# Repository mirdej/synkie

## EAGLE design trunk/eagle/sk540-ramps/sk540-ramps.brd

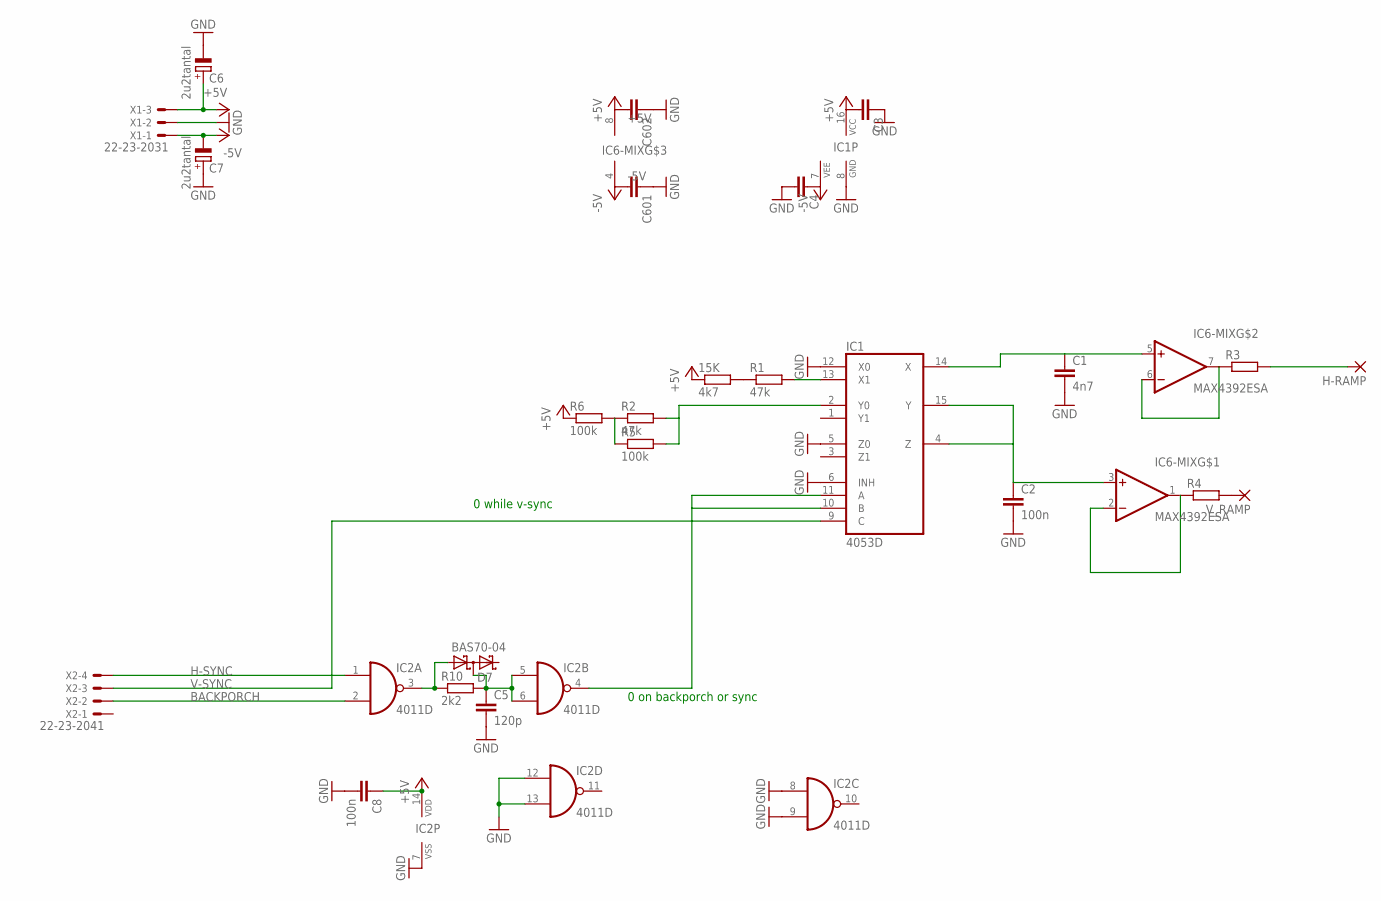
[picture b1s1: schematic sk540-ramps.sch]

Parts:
15K: 4k7; R1206
C1: 4n7; C1206
C2, C8: 100n; C1206
C3, C4, C601, C602: C-EUC1206; C1206
C5: 120p; C1206
C6, C7: 2u2tantal; CT3528
D7: BAS70-04; SOT23
H-RAMP: 3,17/1,1
IC1: 4053D; SO16
IC2: 4011D; SO14
IC6-MIX: MAX4392ESA; SO08
R1, R2: 47k; R1206
R3, R4: R-EU_R1206; R1206
R5, R6: 100k; R1206
R10: 2k2; R1206
V_RAMP: 3,17/1,1
X1: 22-23-2031
X2: 22-23-2041

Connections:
+5V: 15K.1, C3.2, C6.+, C8.1, C602.2, IC1.16 (VCC), IC2.14 (VDD), IC6-MIX.8 (+5V), R6.1, X1.3
-5V: C4.1, C7.-, C601.2, IC1.7 (VEE), IC6-MIX.4 (-5V), X1.1
BACKPORCH: IC2.2 (I1), X2.2
GND: C1.2, C2.2, C3.1, C4.2, C5.2, C6.-, C7.+, C8.2, C601.1, C602.1, IC1.5 (Z0), IC1.6 (INH), IC1.8 (GND), IC1.12 (X0), IC2.7 (VSS), IC2.8 (I0), IC2.9 (I1), IC2.12 (I0), IC2.13 (I1), X1.2
H-SYNC: IC2.1 (I0), X2.4
unnamed: 15K.2, R1.1
unnamed: R2.1, R5.1, R6.2
unnamed: C5.1, D7.3 (C1A2), IC2.5 (I0), IC2.6 (I1), R10.2
unnamed: IC1.10 (B), IC1.11 (A), IC2.4 (O)
unnamed: C1.1, IC1.14 (X), IC6-MIX.5 (+IN)
unnamed: IC6-MIX.6 (-IN), IC6-MIX.7 (OUT), R3.1
unnamed: H-RAMP.1, R3.2
unnamed: C2.1, IC1.4 (Z), IC1.15 (Y), IC6-MIX.3 (+IN)
unnamed: IC6-MIX.1 (OUT), IC6-MIX.2 (-IN), R4.1
unnamed: R4.2, V_RAMP.1
unnamed: D7.1 (A1), IC2.3 (O), R10.1
unnamed: IC1.13 (X1), R1.2
unnamed: IC1.2 (Y0), R2.2, R5.2
V-SYNC: IC1.9 (C), X2.3

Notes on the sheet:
0 on backporch or sync
0 while v-sync

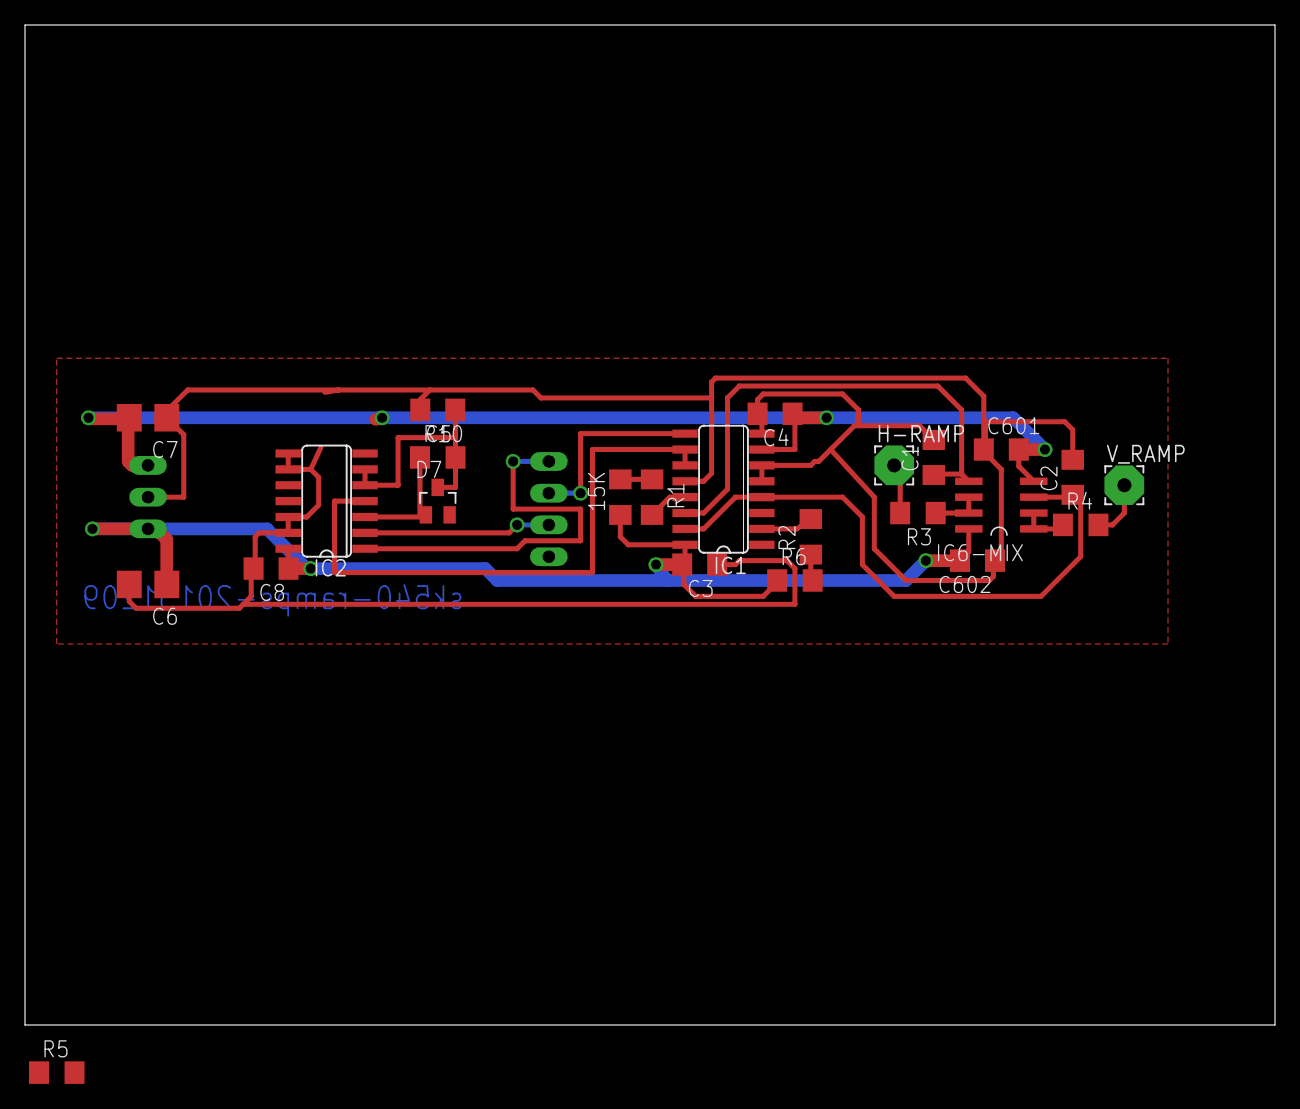
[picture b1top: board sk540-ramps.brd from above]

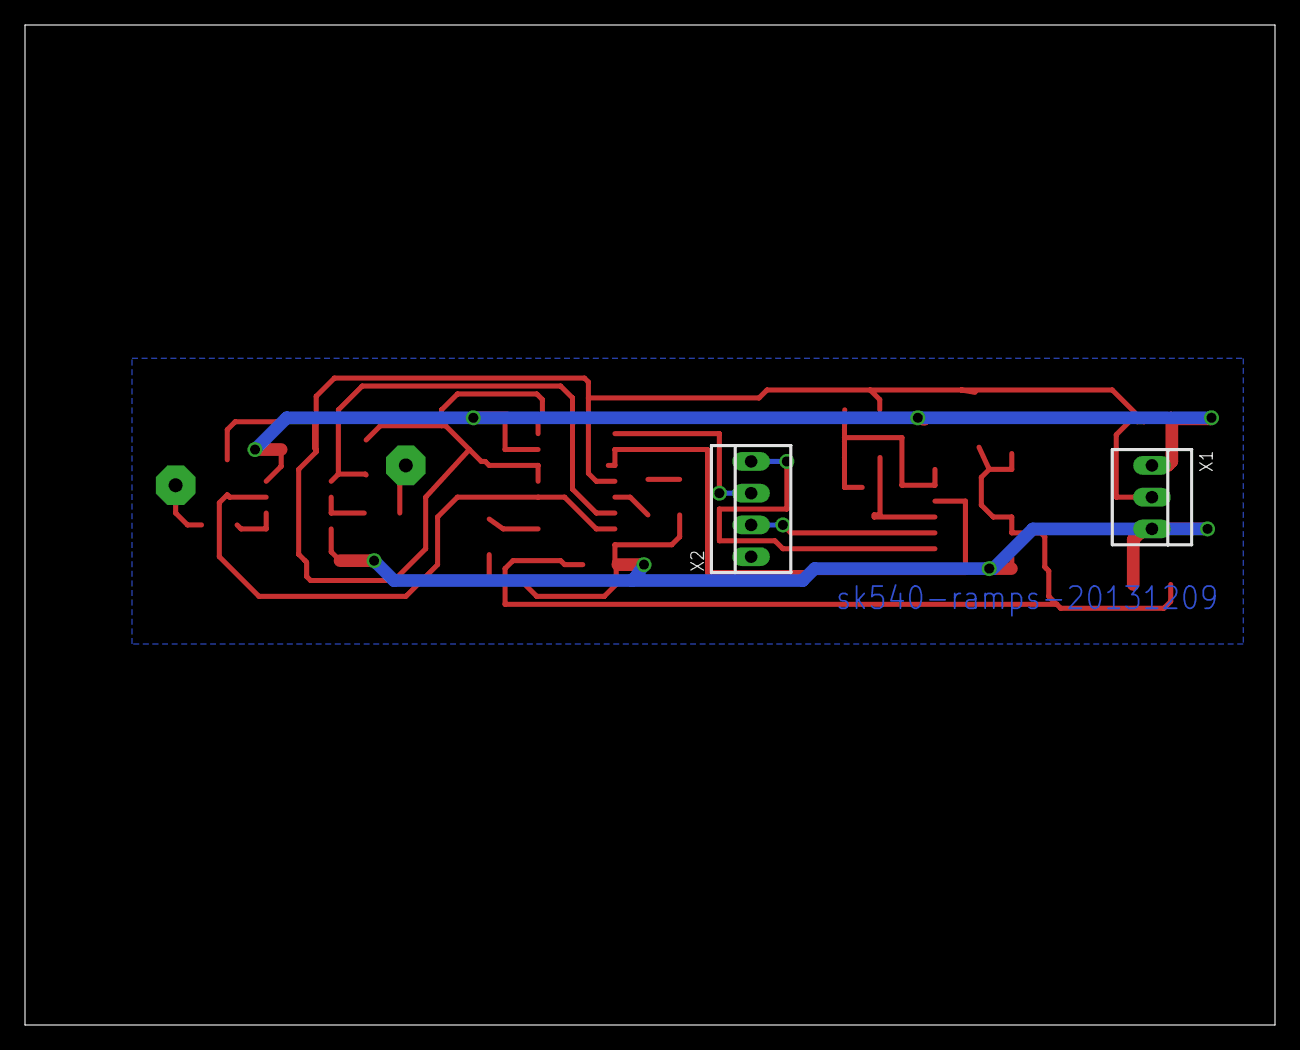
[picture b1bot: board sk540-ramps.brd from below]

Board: 2 copper layers, 100.0 x 80.0 mm, 26 parts (2 on the bottom side), 19 nets.

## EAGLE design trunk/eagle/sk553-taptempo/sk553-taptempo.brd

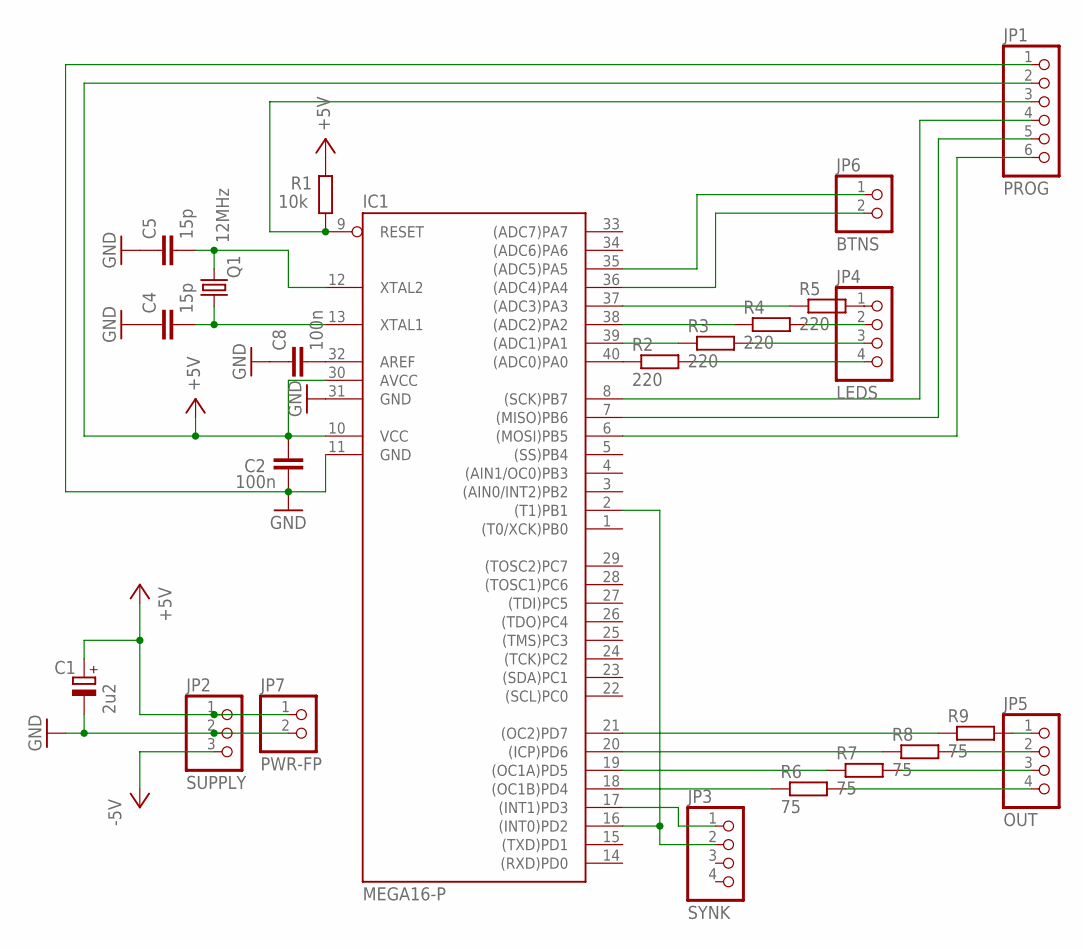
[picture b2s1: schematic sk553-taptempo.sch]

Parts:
C1: 2u2; CT3528
C2, C8: 100n; C0805
C4, C5: 15p; C1206
IC1: MEGA16-P; DIL40
JP1: PROG; 1X06
JP2: SUPPLY; 1X03
JP3: SYNK; 1X04
JP4: LEDS; 1X04
JP5: OUT; 1X04
JP6: BTNS; 1X02
JP7: PWR-FP; 1X02
Q1: 12MHz; HC49UP
R1: 10k; M1206
R2, R3, R4, R5: 220; R1206
R6, R7, R8, R9: 75; R1206

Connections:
+5V: C1.+, C2.1, IC1.10 (VCC), IC1.30 (AVCC), JP1.2, JP2.1, JP7.1, R1.2
-5V: JP2.3
GND: C1.-, C2.2, C4.1, C5.1, C8.1, IC1.11 (GND), IC1.31 (GND), JP1.1, JP2.2, JP7.2
unnamed: IC1.17 ((INT1)PD3), JP3.1
unnamed: IC1.9 (RESET), JP1.3, R1.1
unnamed: IC1.2 ((T1)PB1), IC1.16 ((INT0)PD2), JP3.2
unnamed: IC1.8 ((SCK)PB7), JP1.4
unnamed: IC1.7 ((MISO)PB6), JP1.5
unnamed: C4.2, IC1.13 (XTAL1), Q1.1
unnamed: IC1.6 ((MOSI)PB5), JP1.6
unnamed: IC1.40 ((ADC0)PA0), R2.1
unnamed: IC1.39 ((ADC1)PA1), R3.1
unnamed: IC1.38 ((ADC2)PA2), R4.1
unnamed: C8.2, IC1.32 (AREF)
unnamed: IC1.37 ((ADC3)PA3), R5.1
unnamed: JP4.1, R5.2
unnamed: JP4.4, R2.2
unnamed: JP4.3, R3.2
unnamed: JP4.2, R4.2
unnamed: IC1.35 ((ADC5)PA5), JP6.1
unnamed: IC1.36 ((ADC4)PA4), JP6.2
unnamed: IC1.21 ((OC2)PD7), R9.1
unnamed: IC1.20 ((ICP)PD6), R8.1
unnamed: IC1.19 ((OC1A)PD5), R7.1
unnamed: IC1.18 ((OC1B)PD4), R6.1
unnamed: JP5.1, R9.2
unnamed: JP5.2, R8.2
unnamed: JP5.3, R7.2
unnamed: JP5.4, R6.2
unnamed: C5.2, IC1.12 (XTAL2), Q1.2

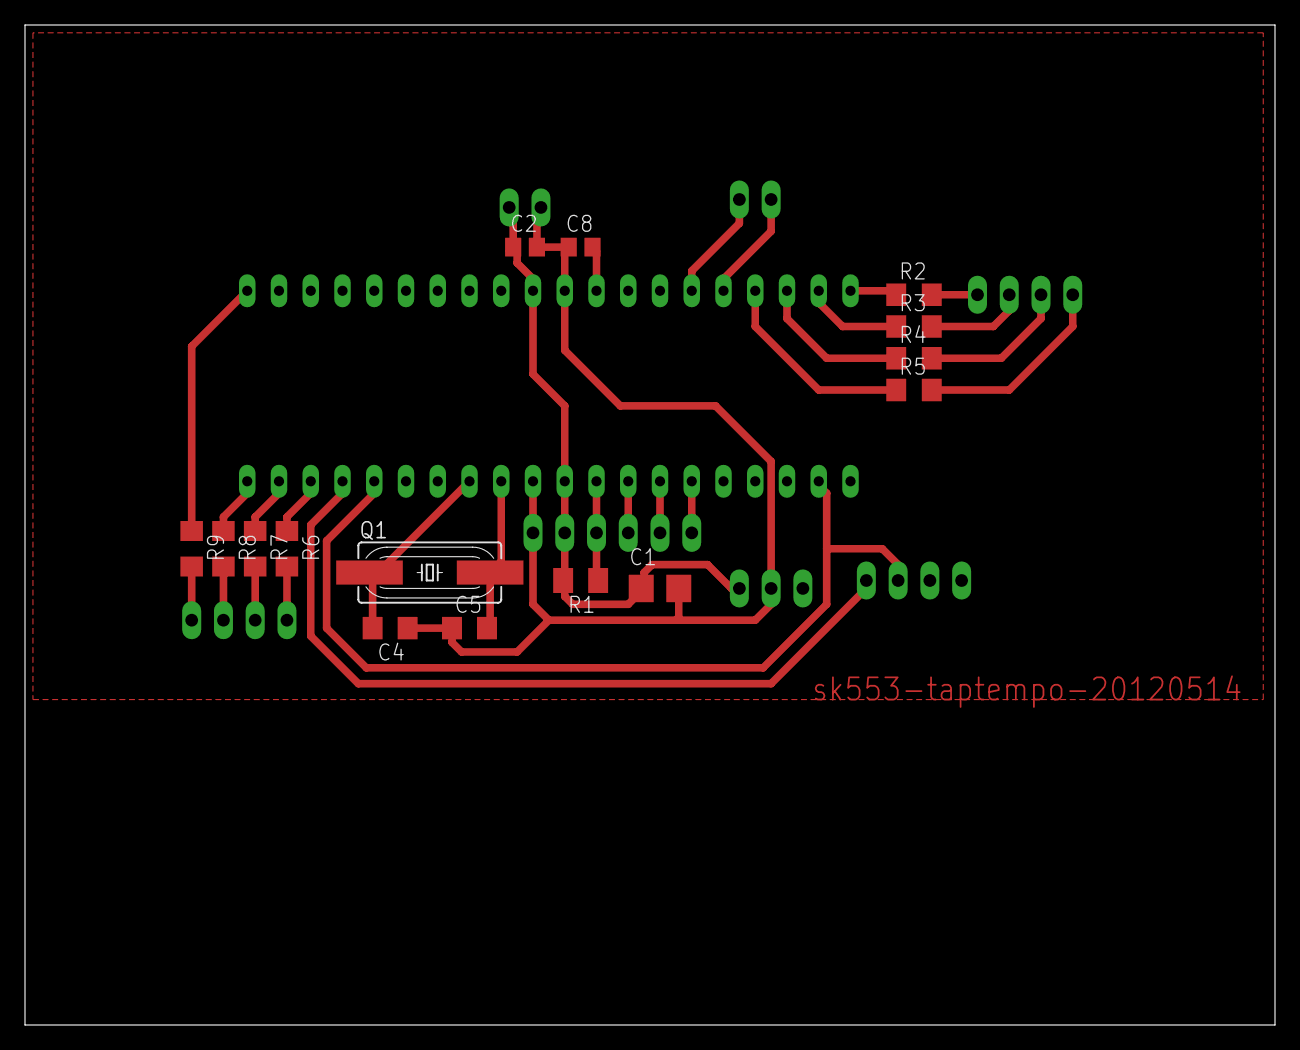
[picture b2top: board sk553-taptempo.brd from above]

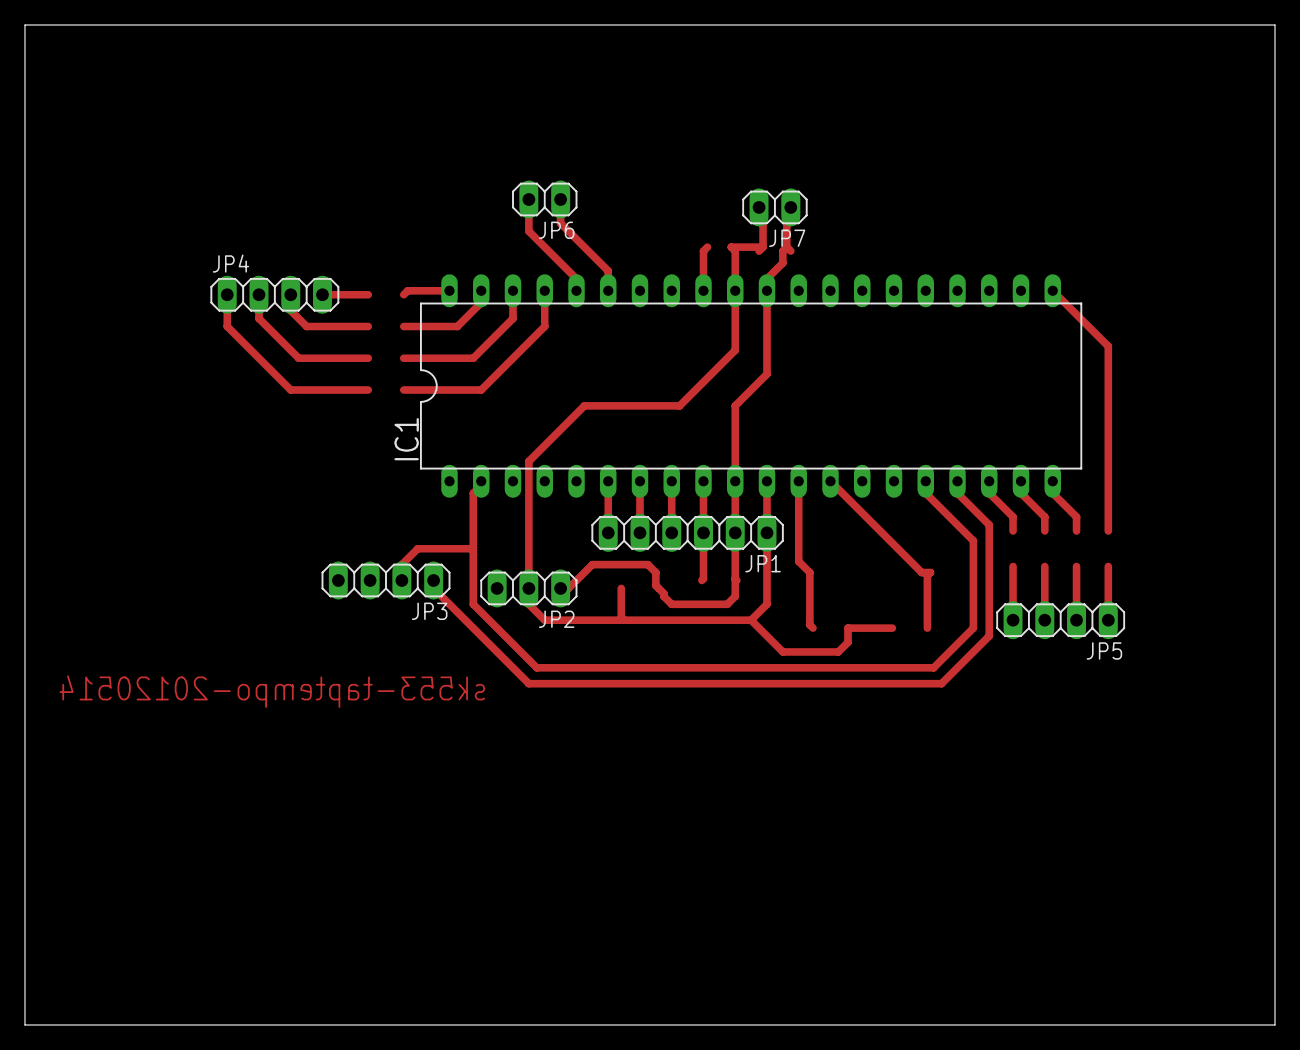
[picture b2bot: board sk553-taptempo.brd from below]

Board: 2 copper layers, 100.0 x 80.0 mm, 23 parts (8 on the bottom side), 29 nets.

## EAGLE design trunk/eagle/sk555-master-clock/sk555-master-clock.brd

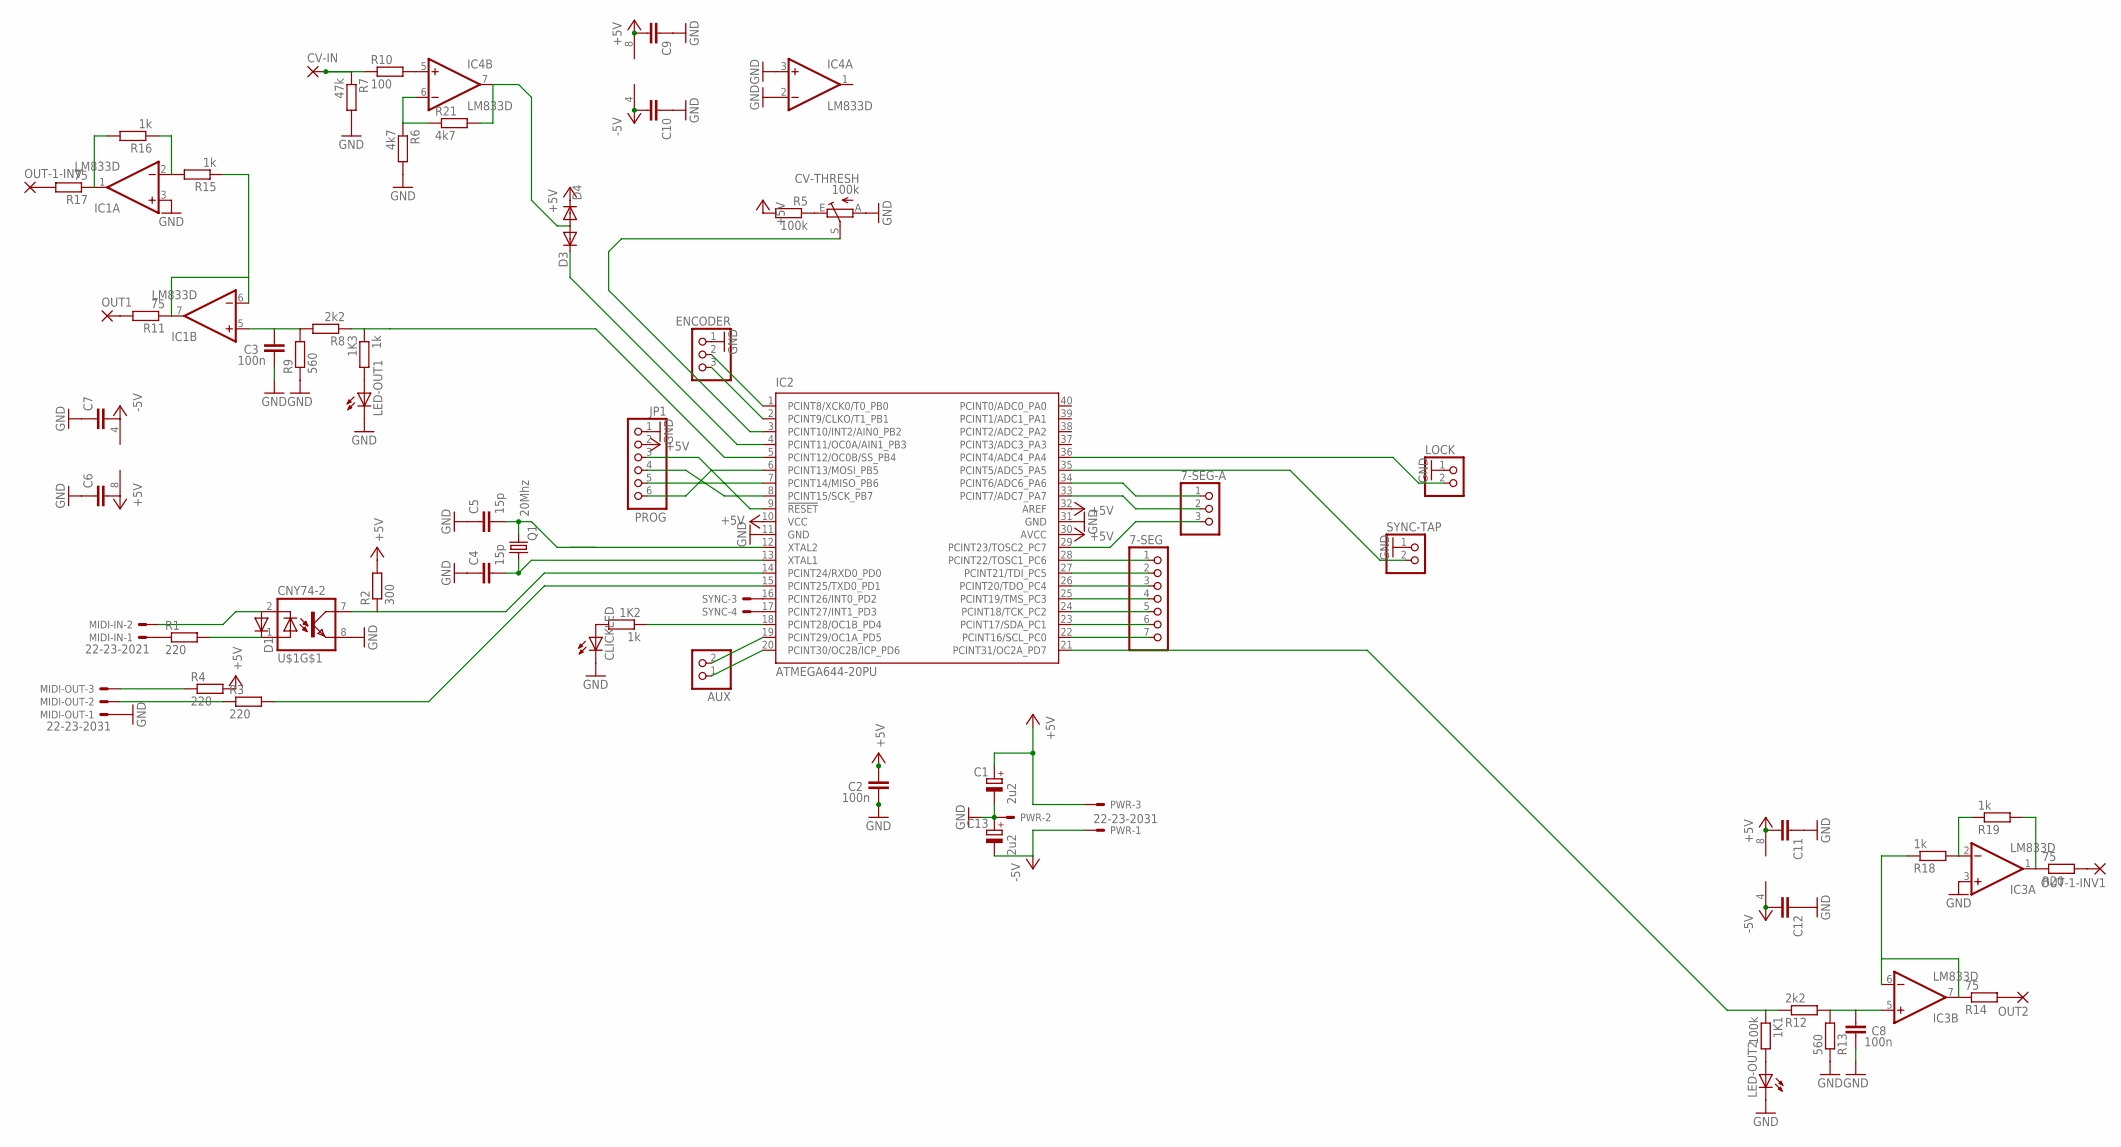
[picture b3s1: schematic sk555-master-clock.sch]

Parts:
1K1: 100k; R1206
1K2, 1K3: 1k; R1206
7-SEG: PINHD-1X7; 1X07
7-SEG-A: PINHD-1X3; 1X03
AUX: PINHD-1X2; 1X02
C1, C13: 2u2; CT3528
C2, C3, C8: 100n; C0805
C4, C5: 15p; C1206
C6, C7, C9, C10: C-EUC1206; C1206
C11, C12: C-EUC0805; C0805
CLICKLED: LED3MM
CV-IN: 3,17/1,1
CV-THRESH: 100k; CIP20C-6MM
D1, D3, D4: DIODE-MINIMELF; MINIMELF
ENCODER: PINHD-1X3; 1X03
IC1, IC3, IC4: LM833D; SO08
IC2: ATMEGA644-20PU; DIL40
JP1: PROG; 1X06
LED-OUT1, LED-OUT2: LED3MM
LOCK: PINHD-1X2; 1X02
MIDI-IN: 22-23-2021
MIDI-OUT: 22-23-2031
OUT1, OUT2: 3,17/1,1
OUT-1-INV, OUT-1-INV1: 3,17/1,1
PWR: 22-23-2031
Q1: 20Mhz; HC49UP
R1, R3, R4: 220; R1206
R2: 300; R1206
R5: 100k; R1206
R6, R21: 4k7; R1206
R7: 47k; R1206
R8, R12: 2k2; R1206
R9, R13: 560; R1206
R10: 100; R1206
R11, R14, R17, R20: 75; R1206
R15, R16, R18, R19: 1k; R1206
SYNC: 22-23-2041
SYNC-TAP: PINHD-1X2; 1X02
U$1: CNY74-2; DIL08

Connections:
+5V: C1.+, C2.1, C6.2, C9.2, C11.2, D4.C, IC1.8 (V+), IC2.10 (VCC), IC2.30 (AVCC), IC2.32 (AREF), IC3.8 (V+), IC4.8 (V+), JP1.2, PWR.3, R2.2, R4.2, R5.2
-5V: C7.2, C10.2, C12.2, C13.-, IC1.4 (V-), IC3.4 (V-), IC4.4 (V-), PWR.1
GND: C1.-, C2.2, C3.2, C4.1, C5.1, C6.1, C7.1, C8.2, C9.1, C10.1, C11.1, C12.1, C13.+, CLICKLED.K (C), CV-THRESH.A, ENCODER.1, IC1.3 (+IN), IC2.11 (GND), IC2.31 (GND), IC3.3 (+IN), IC4.2 (-IN), IC4.3 (+IN), JP1.1, LED-OUT1.K (C), LED-OUT2.K (C), LOCK.1, MIDI-OUT.1, PWR.2, R6.2, R7.2, R9.1, R13.1, SYNC-TAP.1, U$1.8 (EMI)
unnamed: IC2.8 (PCINT15/SCK_PB7), JP1.4
unnamed: IC2.7 (PCINT14/MISO_PB6), JP1.5
unnamed: IC2.6 (PCINT13/MOSI_PB5), JP1.6
unnamed: IC2.9 (!RESET), JP1.3
unnamed: C4.2, IC2.13 (XTAL1), Q1.1
unnamed: MIDI-IN.1, R1.1
unnamed: D1.A, MIDI-IN.2, U$1.2 (C)
unnamed: D1.C, R1.2, U$1.1 (A)
unnamed: IC2.14 (PCINT24/RXD0_PD0), R2.1, U$1.7 (COL)
unnamed: MIDI-OUT.2, R3.1
unnamed: MIDI-OUT.3, R4.1
unnamed: IC2.15 (PCINT25/TXD0_PD1), R3.2
unnamed: CV-IN.1, R7.1, R10.1
unnamed: OUT-1-INV.1, R17.2
unnamed: CV-THRESH.S, IC2.3 (PCINT10/INT2/AIN0_PB2)
unnamed: CV-THRESH.E, R5.1
unnamed: D3.C, IC2.4 (PCINT11/OC0A/AIN1_PB3)
unnamed: OUT1.1, R11.2
unnamed: IC4.5 (+IN), R10.2
unnamed: IC4.6 (-IN), R6.1, R21.1
unnamed: IC2.36 (PCINT4/ADC4_PA4), LOCK.2
unnamed: IC2.35 (PCINT5/ADC5_PA5), SYNC-TAP.2
unnamed: 1K3.1, IC2.5 (PCINT12/OC0B/SS_PB4), R8.1
unnamed: OUT-1-INV1.1, R20.2
unnamed: 1K3.2, LED-OUT1.A
unnamed: IC2.16 (PCINT26/INT0_PD2), SYNC.3
unnamed: IC2.17 (PCINT27/INT1_PD3), SYNC.4
unnamed: IC1.2 (-IN), R15.2, R16.1
unnamed: C3.1, IC1.5 (+IN), R8.2, R9.2
unnamed: IC1.6 (-IN), IC1.7 (OUT), R11.1, R15.1
unnamed: 1K1.1, IC2.21 (PCINT31/OC2A_PD7), R12.1
unnamed: OUT2.1, R14.2
unnamed: 7-SEG.1, IC2.28 (PCINT22/TOSC1_PC6)
unnamed: C8.1, IC3.5 (+IN), R12.2, R13.2
unnamed: IC3.6 (-IN), IC3.7 (OUT), R14.1, R18.1
unnamed: C5.2, IC2.12 (XTAL2), Q1.2
unnamed: 1K1.2, LED-OUT2.A
unnamed: IC3.2 (-IN), R18.2, R19.1
unnamed: IC3.1 (OUT), R19.2, R20.1
unnamed: 7-SEG.2, IC2.27 (PCINT21/TDI_PC5)
unnamed: 7-SEG.3, IC2.26 (PCINT20/TDO_PC4)
unnamed: 7-SEG.4, IC2.25 (PCINT19/TMS_PC3)
unnamed: 7-SEG.5, IC2.24 (PCINT18/TCK_PC2)
unnamed: 7-SEG.6, IC2.23 (PCINT17/SDA_PC1)
unnamed: 7-SEG.7, IC2.22 (PCINT16/SCL_PC0)
unnamed: 7-SEG-A.3, IC2.29 (PCINT23/TOSC2_PC7)
unnamed: 7-SEG-A.2, IC2.33 (PCINT7/ADC7_PA7)
unnamed: 7-SEG-A.1, IC2.34 (PCINT6/ADC6_PA6)
unnamed: 1K2.2, CLICKLED.A
unnamed: 1K2.1, IC2.18 (PCINT28/OC1B_PD4)
unnamed: AUX.1, IC2.20 (PCINT30/OC2B/ICP_PD6)
unnamed: AUX.2, IC2.19 (PCINT29/OC1A_PD5)
unnamed: ENCODER.2, IC2.1 (PCINT8/XCK0/T0_PB0)
unnamed: ENCODER.3, IC2.2 (PCINT9/CLKO/T1_PB1)
unnamed: D3.A, D4.A, IC4.7 (OUT), R21.2
unnamed: IC1.1 (OUT), R16.2, R17.1

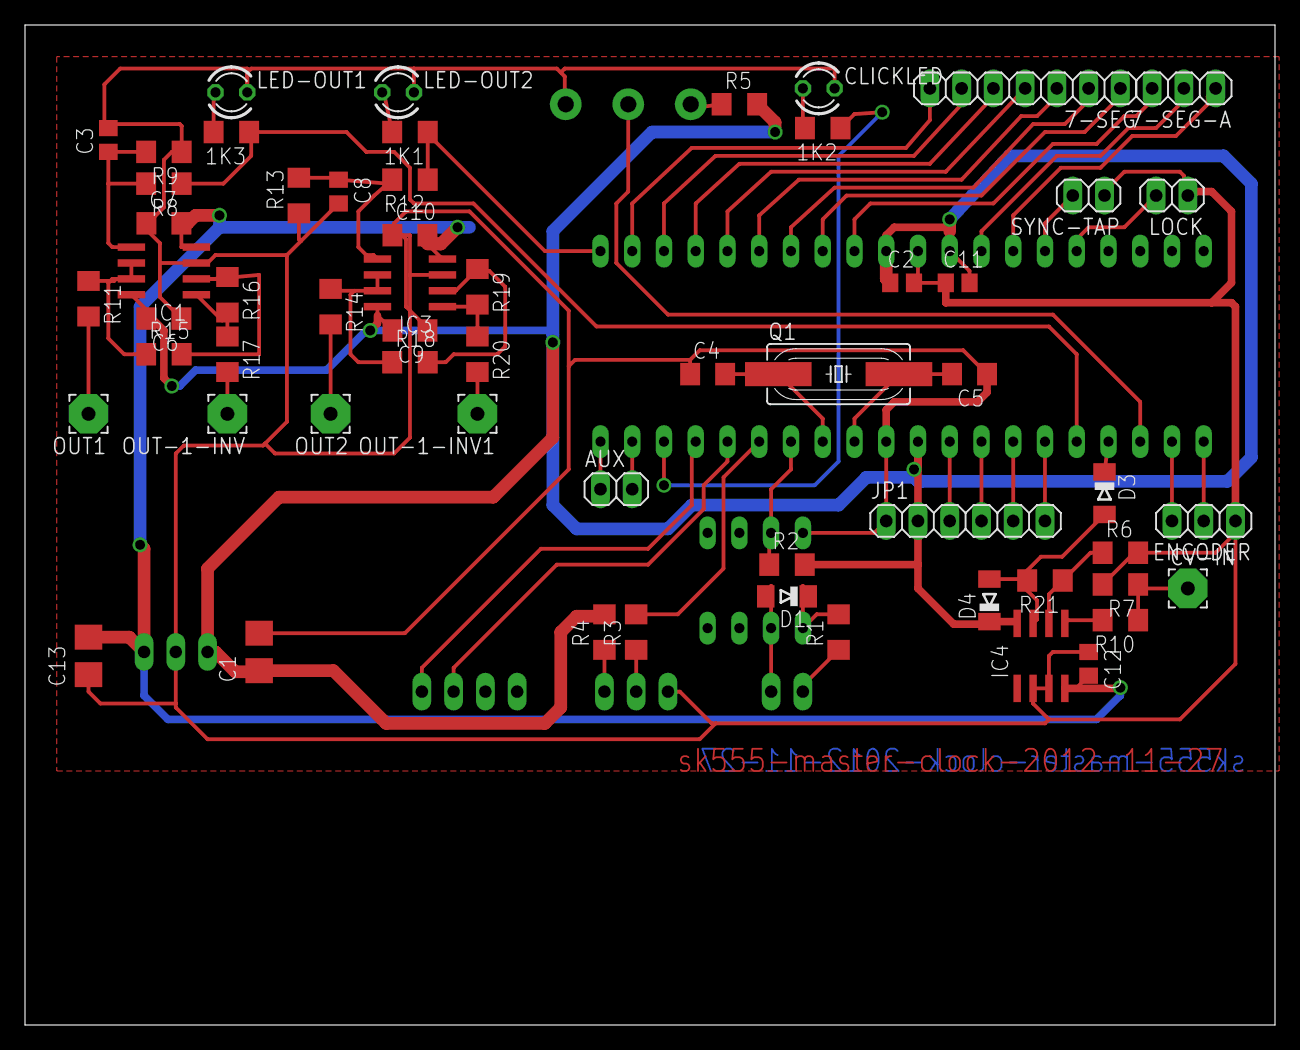
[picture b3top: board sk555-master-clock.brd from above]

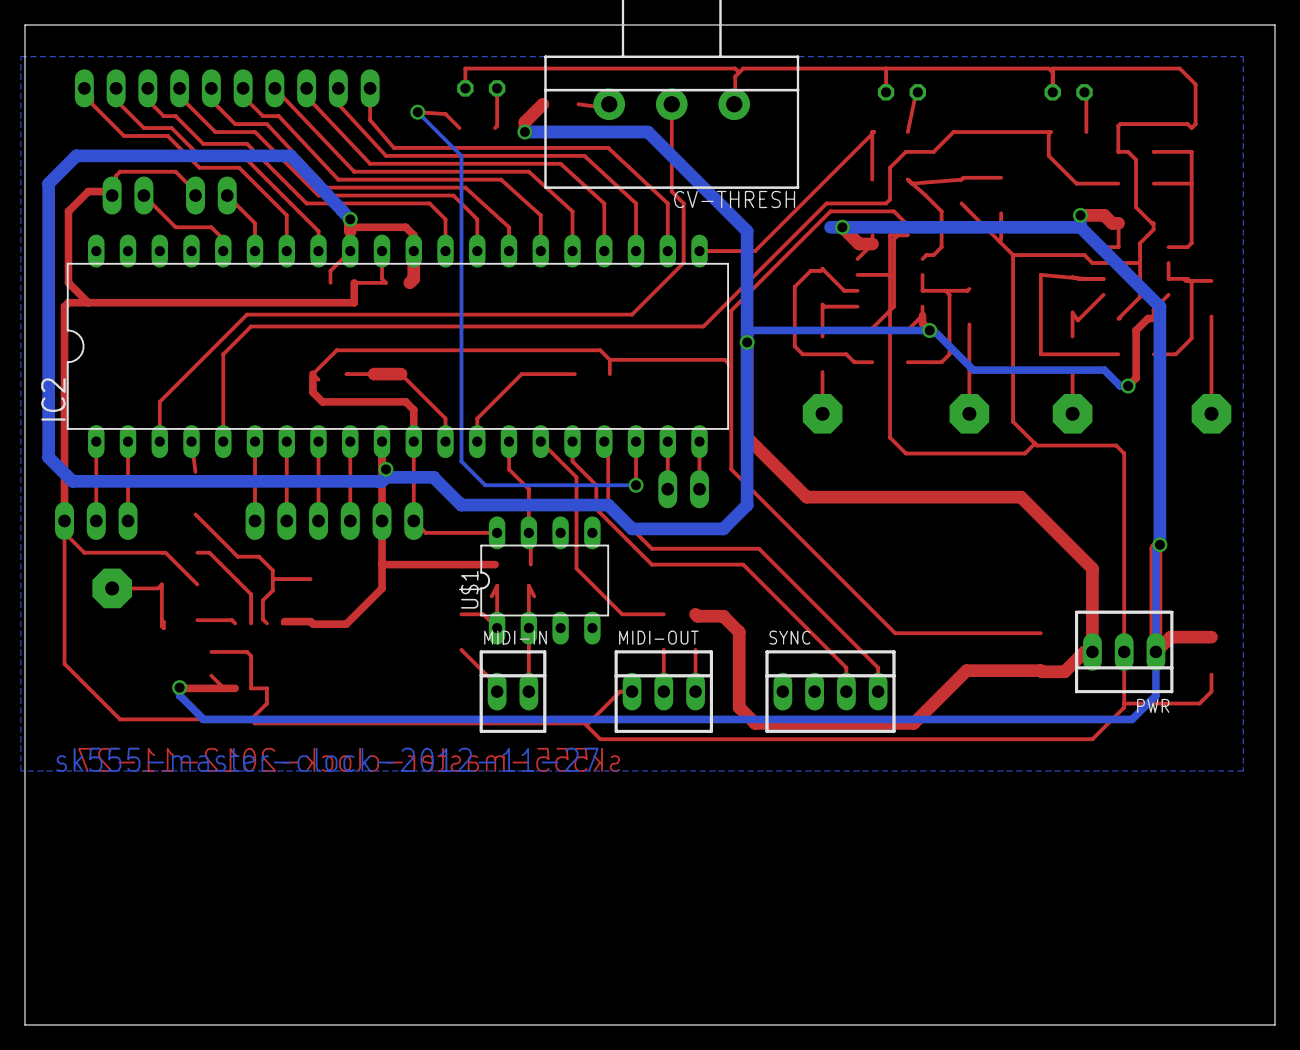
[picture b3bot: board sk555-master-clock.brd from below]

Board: 2 copper layers, 100.0 x 80.0 mm, 66 parts (7 on the bottom side), 59 nets.

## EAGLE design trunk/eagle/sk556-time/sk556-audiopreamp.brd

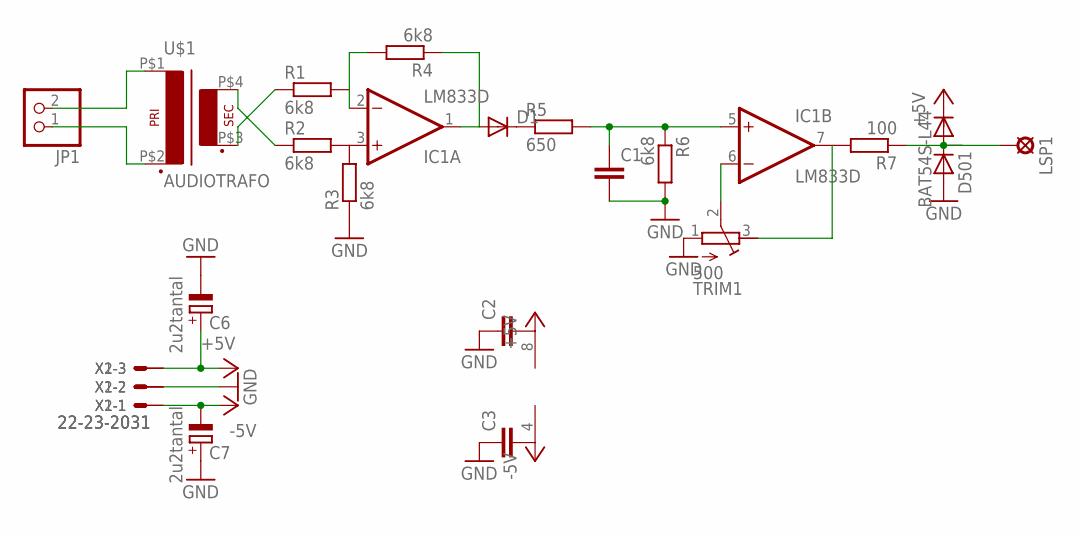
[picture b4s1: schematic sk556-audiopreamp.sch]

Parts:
C1, C2, C3: C-EUC1206; C1206
C6, C7: 2u2tantal; CT3528
D1: DIODE-MINIMELF; MINIMELF
D501: BAT54S-L44; SOT23
IC1: LM833D; SO08
JP1: PINHD-1X2; 1X02
LSP1: SE11
R1, R2, R3, R4, R6: 6k8; R1206
R5: 650; R1206
R7: 100; R1206
TRIM1: 500; RTRIM64Y
U$1: AUDIOTRAFO
X1, X2: 22-23-2031

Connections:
+5V: C2.2, C6.+, D501.2 (C), IC1.8 (V+), X1.3, X2.3
-5V: C3.2, C7.-, IC1.4 (V-), X1.1, X2.1
GND: C1.2, C2.1, C3.1, C6.-, C7.+, D501.1 (A), R3.1, R6.2, TRIM1.1 (E), X1.2, X2.2
unnamed: JP1.2, U$1.P$1 (P1)
unnamed: JP1.1, U$1.P$2 (P2)
unnamed: R1.1, U$1.P$3 (S3)
unnamed: R2.1, U$1.P$4 (S4)
unnamed: IC1.3 (+IN), R2.2, R3.2
unnamed: IC1.2 (-IN), R1.2, R4.2
unnamed: D1.A, IC1.1 (OUT), R4.1
unnamed: C1.1, IC1.5 (+IN), R5.2, R6.1
unnamed: IC1.6 (-IN), TRIM1.2 (S)
unnamed: IC1.7 (OUT), R7.2, TRIM1.3 (A)
unnamed: D501.3 (AC), LSP1.MP, R7.1
unnamed: D1.C, R5.1

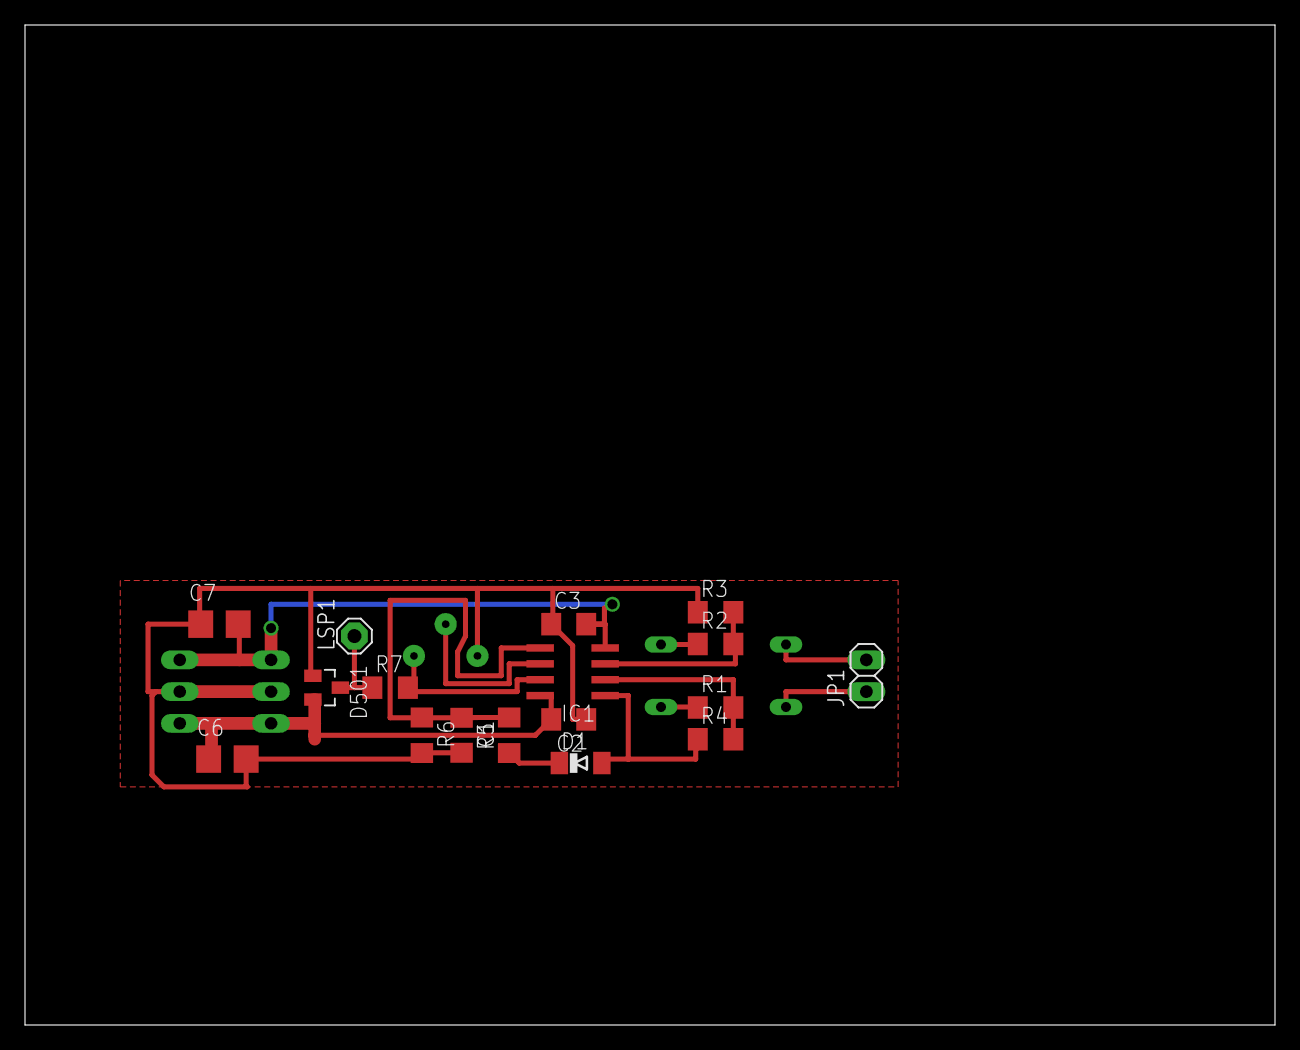
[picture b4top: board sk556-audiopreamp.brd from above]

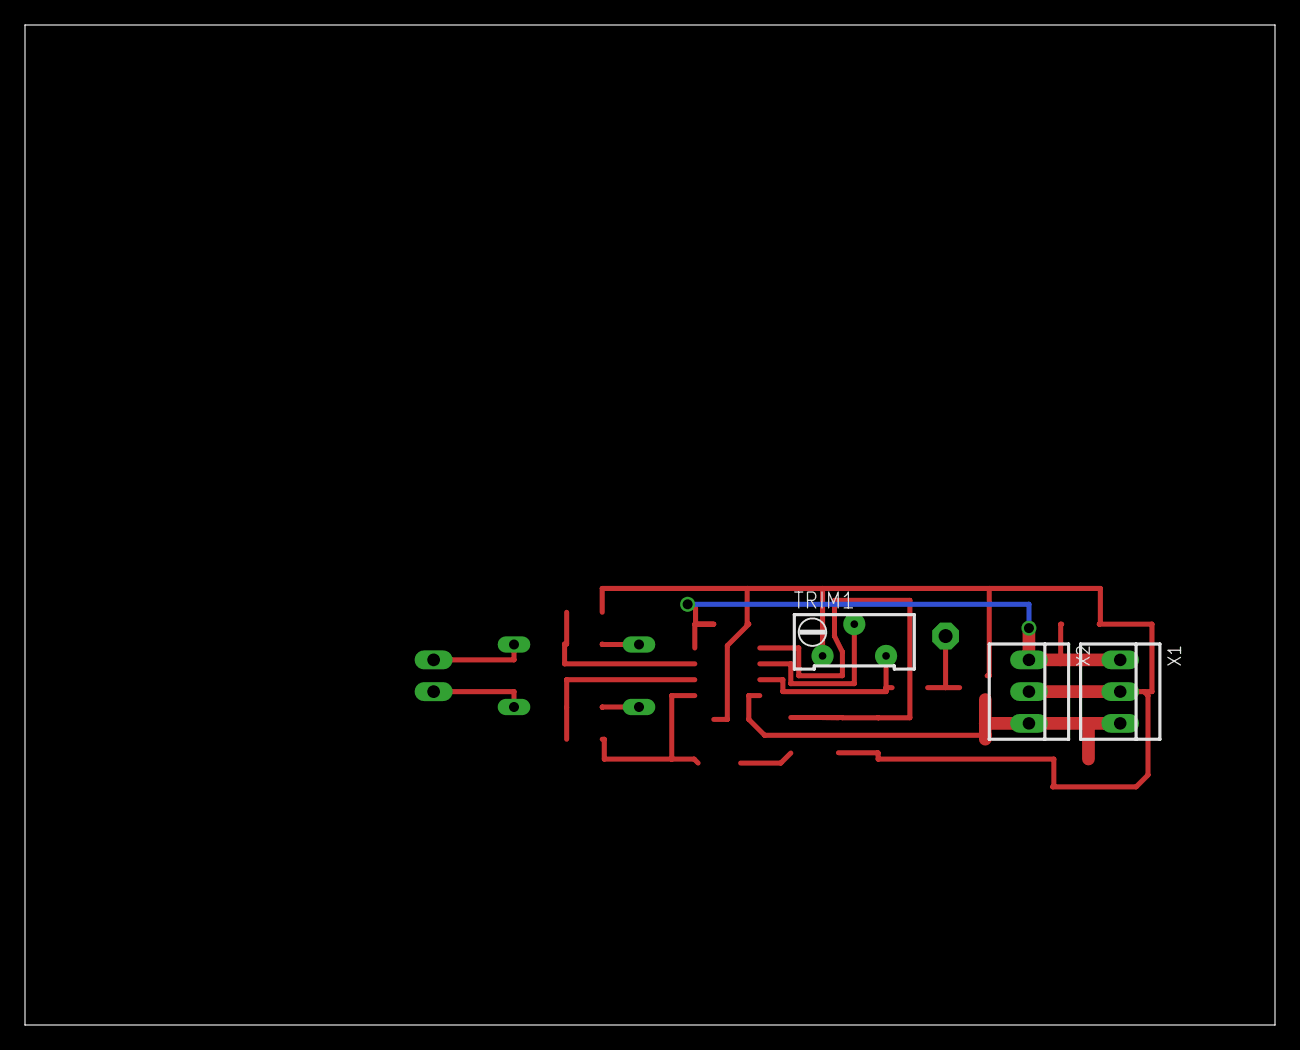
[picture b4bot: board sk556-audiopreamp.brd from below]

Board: 2 copper layers, 100.0 x 80.0 mm, 21 parts (4 on the bottom side), 15 nets.
